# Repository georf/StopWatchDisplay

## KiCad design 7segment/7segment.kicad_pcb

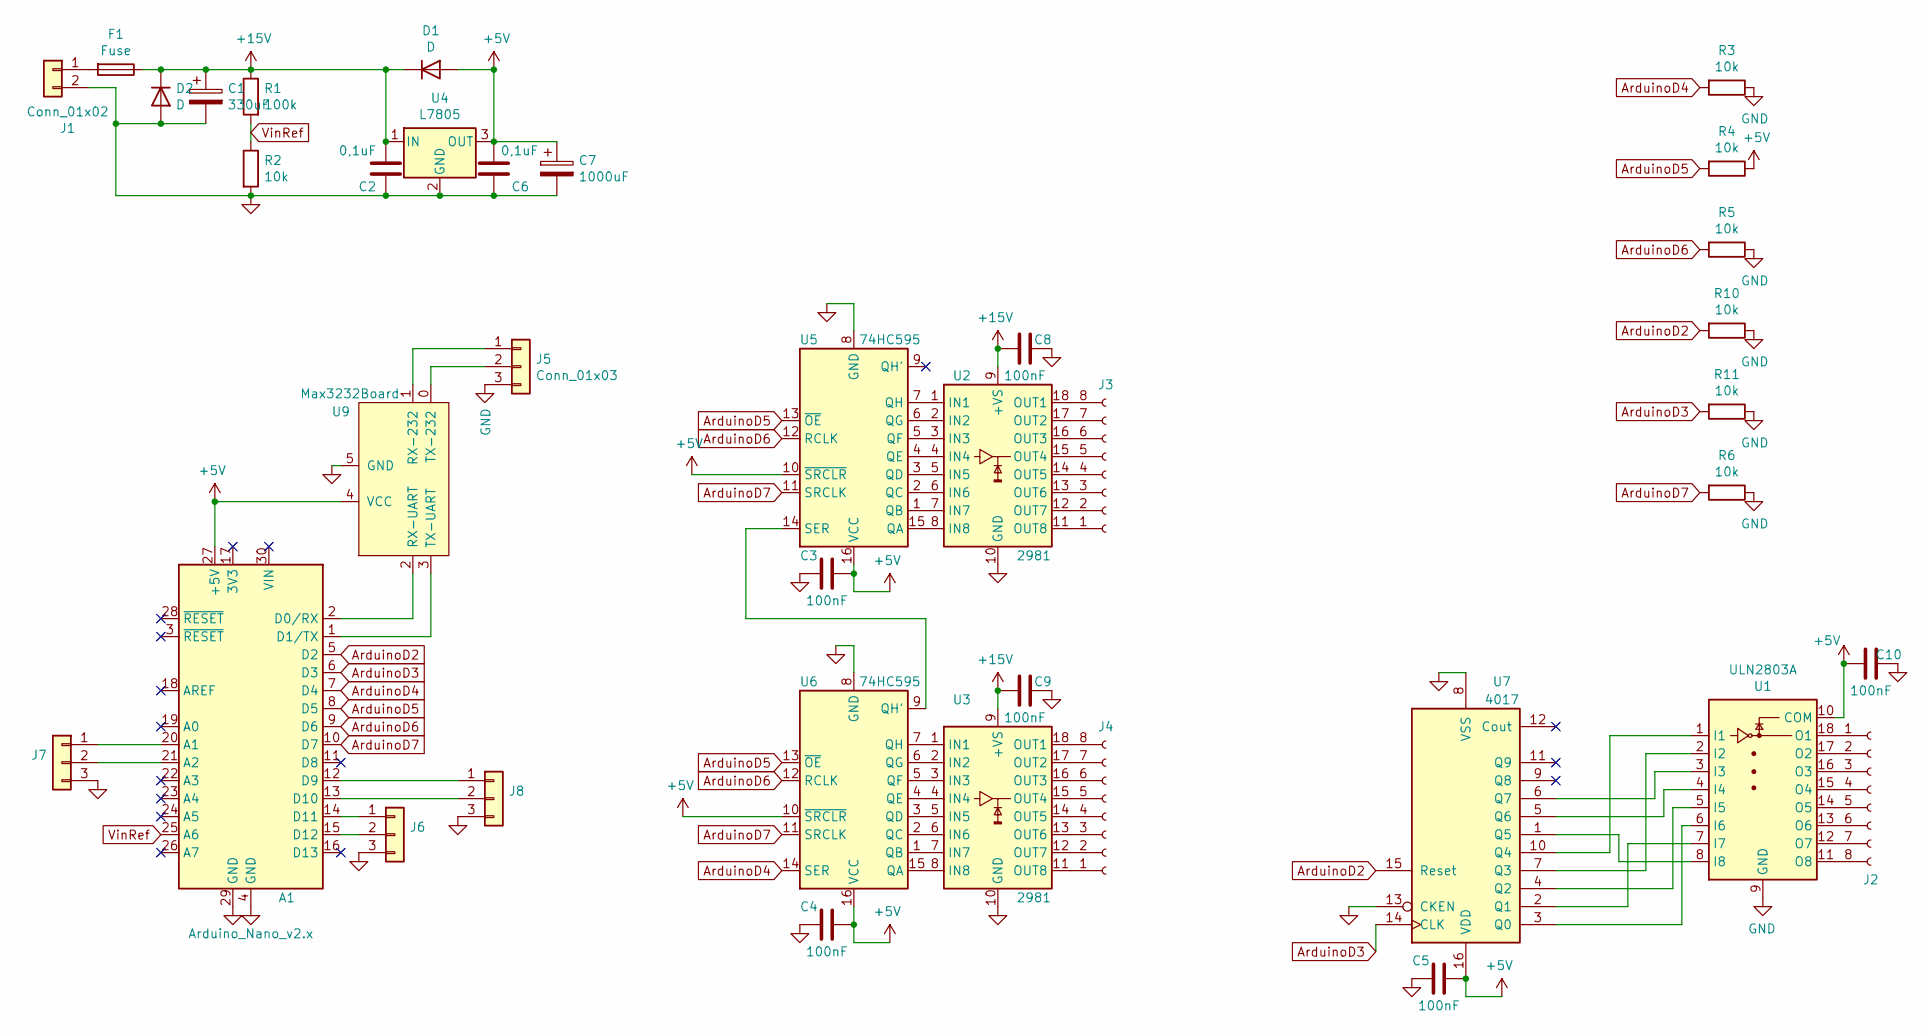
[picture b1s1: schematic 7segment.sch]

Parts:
A1: Arduino_Nano_v2.x; Arduino_Nano
C1: 330uF; CP_Radial_D10.0mm_P5.00mm
C2, C6: 0,1uF; C_Disc_D3.4mm_W2.1mm_P2.50mm
C3, C4, C5, C8, C9, C10: 100nF; C_Disc_D5.0mm_W2.5mm_P2.50mm
C7: 1000uF; CP_Radial_D10.0mm_P5.00mm
D1: D; D_A-405_P10.16mm_Horizontal
D2: D; D_A-405_P7.62mm_Horizontal
F1: Fuse
J1: Conn_01x02; Connector 2xPin
J2, J3, J4: Conn_Segments; PinSocket_1x08_P2.54mm_Vertical
J5, J6, J7, J8: Conn_01x03; Connector 3xPin
R1: 100k; Resistor, L6mm,4holes
R2, R4, R6, R11: 10k; Resistor, L6mm,5holes
R3, R10: 10k; Resistor, L6mm,4holes
R5: 10k; Resistor, L6mm,6holes
U1: ULN2803A; DIP-18_W7.62mm_LongPads
U2, U3: 2981; DIP-18_W7.62mm_LongPads
U4: L7805; TO255P1040X460X1968-3
U5, U6: 74HC595; DIP-16_W7.62mm_LongPads
U7: 4017; DIP-16_W7.62mm_LongPads
U9: Max3232Board; MAX232

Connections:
+5V: A1.27 (+5V), C3.2, C4.2, C5.2, C6.2, C7.1, C10.1, D1.2 (A), R4.1, U1.10 (COM), U4.3 (OUT), U5.10 (~SRCLR), U5.16 (VCC), U6.10 (~SRCLR), U6.16 (VCC), U7.16 (VDD), U9.4 (VCC)
+15V: C1.1, C2.2, C8.1, C9.1, D1.1 (K), D2.1 (K), F1.1, R1.1, U2.9 (+VS), U3.9 (+VS), U4.1 (IN)
ArduinoD2: A1.5 (D2), R10.2, U7.15 (Reset)
ArduinoD3: A1.6 (D3), R11.2, U7.14 (CLK)
ArduinoD4: A1.7 (D4), R3.2, U6.14 (SER)
ArduinoD5: A1.8 (D5), R4.2, U5.13 (~OE), U6.13 (~OE)
ArduinoD6: A1.9 (D6), R5.2, U5.12 (RCLK), U6.12 (RCLK)
ArduinoD7: A1.10 (D7), R6.2, U5.11 (SRCLK), U6.11 (SRCLK)
GND: A1.4 (GND), A1.29 (GND), C1.2, C2.1, C3.1, C4.1, C5.1, C6.1, C7.2, C8.2, C9.2, C10.2, D2.2 (A), J1.2, J5.3, J6.3, J7.3, J8.3, R2.2, R3.1, R5.1, R6.1, R10.1, R11.1, U1.9 (GND), U2.10 (GND), U3.10 (GND), U4.2 (GND), U5.8 (GND), U6.8 (GND), U7.8 (VSS), U7.13 (CKEN), U9.5 (GND)
unnamed: A1.1 (D1/TX), U9.3 (TX-UART)
unnamed: A1.2 (D0/RX), U9.2 (RX-UART)
unnamed: A1.12 (D9), J8.1
unnamed: A1.13 (D10), J8.2
unnamed: A1.14 (D11), J6.1
unnamed: A1.15 (D12), J6.2
unnamed: A1.20 (A1), J7.1
unnamed: A1.21 (A2), J7.2
unnamed: F1.2, J1.1
unnamed: J2.1, U1.18 (O1)
unnamed: J2.2, U1.17 (O2)
unnamed: J2.3, U1.16 (O3)
unnamed: J2.4, U1.15 (O4)
unnamed: J2.5, U1.14 (O5)
unnamed: J2.6, U1.13 (O6)
unnamed: J2.7, U1.12 (O7)
unnamed: J2.8, U1.11 (O8)
unnamed: J3.1, U2.11 (NC)
unnamed: J3.2, U2.12 (OUT7)
unnamed: J3.3, U2.13 (OUT6)
unnamed: J3.4, U2.14 (OUT5)
unnamed: J3.5, U2.15 (OUT4)
unnamed: J3.6, U2.16 (OUT3)
unnamed: J3.7, U2.17 (OUT2)
unnamed: J3.8, U2.18 (OUT1)
unnamed: J4.1, U3.11 (NC)
unnamed: J4.2, U3.12 (OUT7)
unnamed: J4.3, U3.13 (OUT6)
unnamed: J4.4, U3.14 (OUT5)
unnamed: J4.5, U3.15 (OUT4)
unnamed: J4.6, U3.16 (OUT3)
unnamed: J4.7, U3.17 (OUT2)
unnamed: J4.8, U3.18 (OUT1)
unnamed: J5.1, U9.1 (RX-232)
unnamed: J5.2, U9.0 (TX-232)
unnamed: U1.1 (I1), U7.10 (Q4)
unnamed: U1.2 (I2), U7.7 (Q3)
unnamed: U1.3 (I3), U7.6 (Q7)
unnamed: U1.4 (I4), U7.5 (Q6)
unnamed: U1.5 (I5), U7.4 (Q2)
unnamed: U1.6 (I6), U7.3 (Q0)
unnamed: U1.7 (I7), U7.2 (Q1)
unnamed: U1.8 (I8), U7.1 (Q5)
unnamed: U2.1 (IN1), U5.7 (QH)
unnamed: U2.2 (IN2), U5.6 (QG)
unnamed: U2.3 (IN3), U5.5 (QF)
unnamed: U2.4 (IN4), U5.4 (QE)
unnamed: U2.5 (IN5), U5.3 (QD)
unnamed: U2.6 (IN6), U5.2 (QC)
unnamed: U2.7 (IN7), U5.1 (QB)
unnamed: U2.8 (IN8), U5.15 (QA)
unnamed: U3.1 (IN1), U6.7 (QH)
unnamed: U3.2 (IN2), U6.6 (QG)
unnamed: U3.3 (IN3), U6.5 (QF)
unnamed: U3.4 (IN4), U6.4 (QE)
unnamed: U3.5 (IN5), U6.3 (QD)
unnamed: U3.6 (IN6), U6.2 (QC)
unnamed: U3.7 (IN7), U6.1 (QB)
unnamed: U3.8 (IN8), U6.15 (QA)
unnamed: U5.14 (SER), U6.9 (QH')
VinRef: A1.25 (A6), R1.2, R2.1

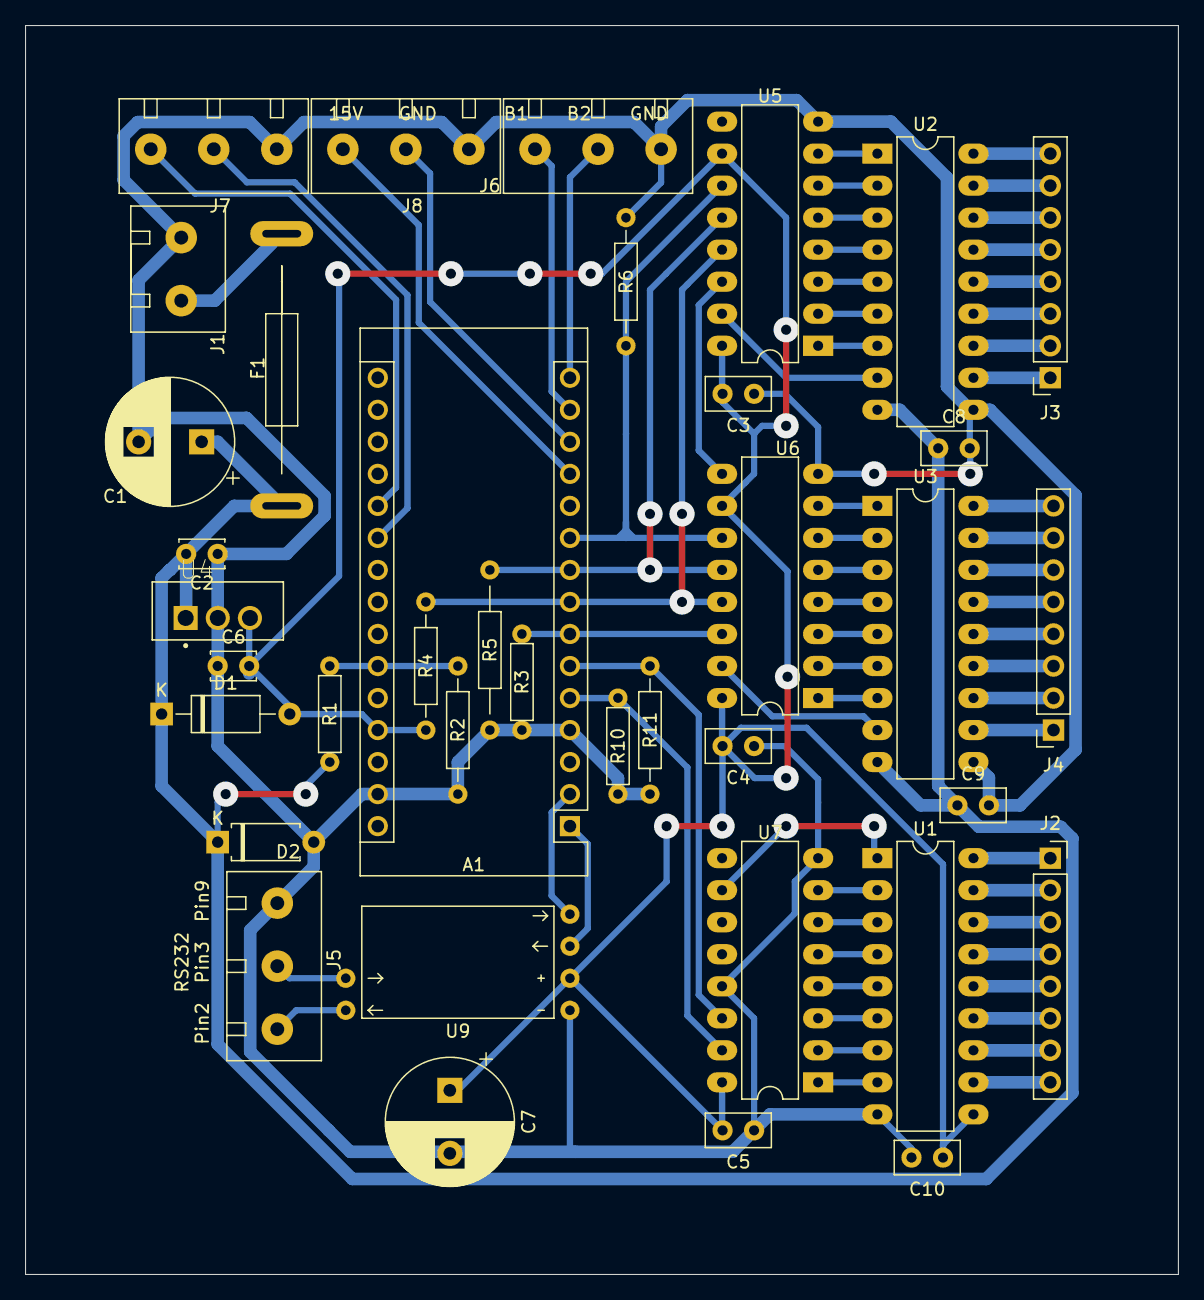
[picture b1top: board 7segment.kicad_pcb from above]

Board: 2 copper layers, 91.4 x 99.1 mm, 38 parts (0 on the bottom side), 70 nets.

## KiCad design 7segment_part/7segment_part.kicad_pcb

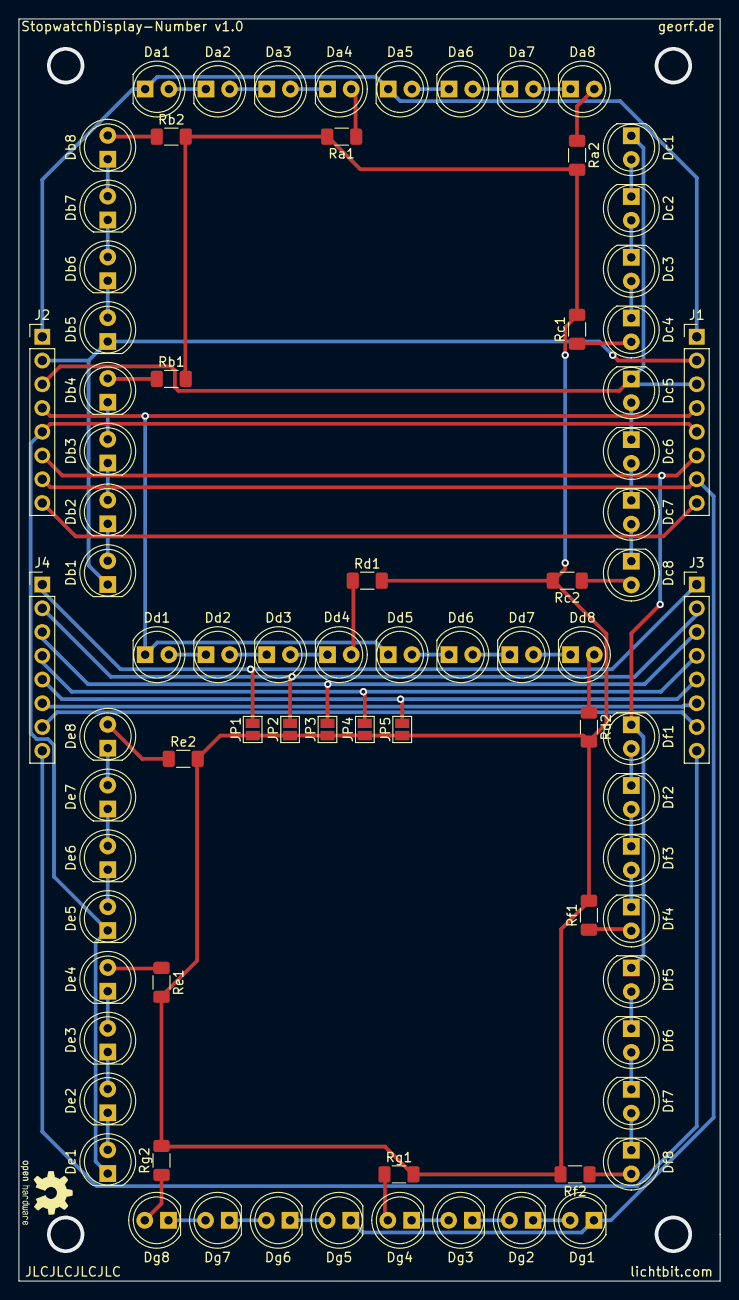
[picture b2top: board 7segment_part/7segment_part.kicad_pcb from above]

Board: 2 copper layers, 75.0 x 135.0 mm, 79 parts (0 on the bottom side), 73 nets.

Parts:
Da1, Da2, Da3, Da4, Da5, Da6, Da7, Da8: LED; LED_D5.0mm_Clear
Db1, Db2, Db3, Db4, Db5, Db6, Db7, Db8: LED; LED_D5.0mm_Clear
Dc1, Dc2, Dc3, Dc4, Dc5, Dc6, Dc7, Dc8: LED; LED_D5.0mm_Clear
Dd1, Dd2, Dd3, Dd4, Dd5, Dd6, Dd7, Dd8: LED; LED_D5.0mm_Clear
De1, De2, De3, De4, De5, De6, De7, De8: LED; LED_D5.0mm_Clear
Df1, Df2, Df3, Df4, Df5, Df6, Df7, Df8: LED; LED_D5.0mm_Clear
Dg1, Dg2, Dg3, Dg4, Dg5, Dg6, Dg7, Dg8: LED; LED_D5.0mm_Clear
J1, J2: Segments; PinHeader_1x08_P2.54mm_Vertical
J3, J4: Numbers; PinHeader_1x08_P2.54mm_Vertical
JP1, JP2, JP3, JP4, JP5: SolderJumper_2_Open; SolderJumper-2_P1.3mm_Open_Pad1.0x1.5mm
Ra1, Ra2: R; R_1206_3216Metric_Pad1.30x1.75mm_HandSolder
Rb1, Rb2: R; R_1206_3216Metric_Pad1.30x1.75mm_HandSolder
Rc1, Rc2: R; R_1206_3216Metric_Pad1.30x1.75mm_HandSolder
Rd1, Rd2: R; R_1206_3216Metric_Pad1.30x1.75mm_HandSolder
Re1, Re2: R; R_1206_3216Metric_Pad1.30x1.75mm_HandSolder
Rf1, Rf2: R; R_1206_3216Metric_Pad1.30x1.75mm_HandSolder
Rg1, Rg2: R; R_1206_3216Metric_Pad1.30x1.75mm_HandSolder

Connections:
unnamed: Da1.1, Da5.1, J1.1, J2.1
unnamed: Da1.2, Da2.1
unnamed: Da2.2, Da3.1
unnamed: Da3.2, Da4.1
unnamed: Da4.2, Ra1.1
unnamed: Da5.2, Da6.1
unnamed: Da6.2, Da7.1
unnamed: Da7.2, Da8.1
unnamed: Da8.2, Ra2.1
unnamed: Db1.1, Db5.1, J1.2, J2.2
unnamed: Db1.2, Db2.1
unnamed: Db2.2, Db3.1
unnamed: Db3.2, Db4.1
unnamed: Db4.2, Rb1.1
unnamed: Db5.2, Db6.1
unnamed: Db6.2, Db7.1
unnamed: Db7.2, Db8.1
unnamed: Db8.2, Rb2.1
unnamed: Dc1.1, Dc5.1, J1.3, J2.3
unnamed: Dc1.2, Dc2.1
unnamed: Dc2.2, Dc3.1
unnamed: Dc3.2, Dc4.1
unnamed: Dc4.2, Rc1.1
unnamed: Dc5.2, Dc6.1
unnamed: Dc6.2, Dc7.1
unnamed: Dc7.2, Dc8.1
unnamed: Dc8.2, Rc2.1
unnamed: Dd1.1, Dd5.1, J1.4, J2.4
unnamed: Dd1.2, Dd2.1
unnamed: Dd2.2, Dd3.1
unnamed: Dd3.2, Dd4.1
unnamed: Dd4.2, Rd1.1
unnamed: Dd5.2, Dd6.1
unnamed: Dd6.2, Dd7.1
unnamed: Dd7.2, Dd8.1
unnamed: Dd8.2, Rd2.1
unnamed: De1.1, De5.1, J1.5, J2.5
unnamed: De1.2, De2.1
unnamed: De2.2, De3.1
unnamed: De3.2, De4.1
unnamed: De4.2, Re1.1
unnamed: De5.2, De6.1
unnamed: De6.2, De7.1
unnamed: De7.2, De8.1
unnamed: De8.2, Re2.1
unnamed: Df1.1, Df5.1, J1.6, J2.6
unnamed: Df1.2, Df2.1
unnamed: Df2.2, Df3.1
unnamed: Df3.2, Df4.1
unnamed: Df4.2, Rf1.1
unnamed: Df5.2, Df6.1
unnamed: Df6.2, Df7.1
unnamed: Df7.2, Df8.1
unnamed: Df8.2, Rf2.1
unnamed: Dg1.1, Dg5.1, J1.7, J2.7
unnamed: Dg1.2, Dg2.1
unnamed: Dg2.2, Dg3.1
unnamed: Dg3.2, Dg4.1
unnamed: Dg4.2, Rg1.1
unnamed: Dg5.2, Dg6.1
unnamed: Dg6.2, Dg7.1
unnamed: Dg7.2, Dg8.1
unnamed: Dg8.2, Rg2.1
unnamed: J1.8, J2.8
unnamed: J3.1, J4.1, JP1.2
unnamed: J3.2, J4.2, JP2.2
unnamed: J3.3, J4.3, JP3.2
unnamed: J3.4, J4.4, JP4.2
unnamed: J3.5, J4.5, JP5.2
unnamed: J3.6, J4.6
unnamed: J3.7, J4.7
unnamed: J3.8, J4.8
unnamed: JP1.1, JP2.1, JP3.1, JP4.1, JP5.1, Ra1.2, Ra2.2, Rb1.2, Rb2.2, Rc1.2, Rc2.2, Rd1.2, Rd2.2, Re1.2, Re2.2, Rf1.2, Rf2.2, Rg1.2, Rg2.2

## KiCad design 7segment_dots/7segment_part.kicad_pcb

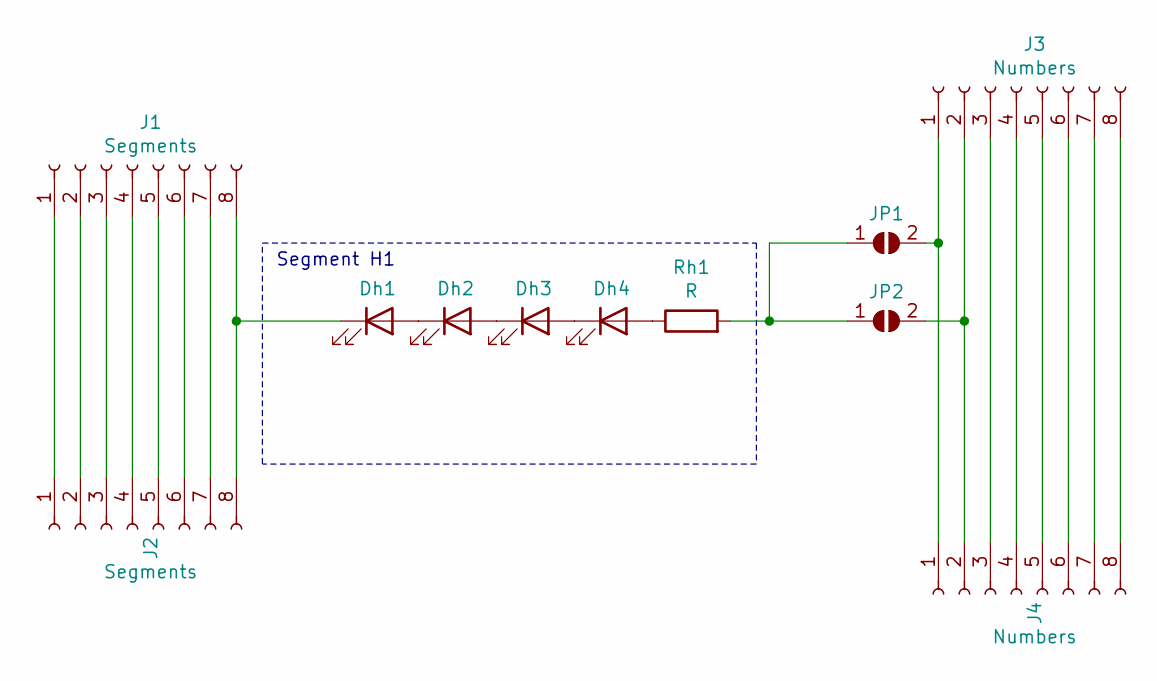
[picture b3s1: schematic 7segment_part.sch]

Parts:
Dh1, Dh2, Dh3, Dh4: LED; LED_D5.0mm_Clear
J1, J2: Segments; PinHeader_1x08_P2.54mm_Vertical
J3, J4: Numbers; PinHeader_1x08_P2.54mm_Vertical
JP1, JP2: SolderJumper_2_Open; SolderJumper-2_P1.3mm_Open_Pad1.0x1.5mm
Rh1: R; R_1206_3216Metric_Pad1.30x1.75mm_HandSolder

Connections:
unnamed: Dh1.1 (K), J1.8, J2.8
unnamed: Dh1.2 (A), Dh2.1 (K)
unnamed: Dh2.2 (A), Dh3.1 (K)
unnamed: Dh3.2 (A), Dh4.1 (K)
unnamed: Dh4.2 (A), Rh1.1
unnamed: J1.1, J2.1
unnamed: J1.2, J2.2
unnamed: J1.3, J2.3
unnamed: J1.4, J2.4
unnamed: J1.5, J2.5
unnamed: J1.6, J2.6
unnamed: J1.7, J2.7
unnamed: J3.1, J4.1, JP1.2 (B)
unnamed: J3.2, J4.2, JP2.2 (B)
unnamed: J3.3, J4.3
unnamed: J3.4, J4.4
unnamed: J3.5, J4.5
unnamed: J3.6, J4.6
unnamed: J3.7, J4.7
unnamed: J3.8, J4.8
unnamed: JP1.1 (A), JP2.1 (A), Rh1.2

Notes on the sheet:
Segment H1

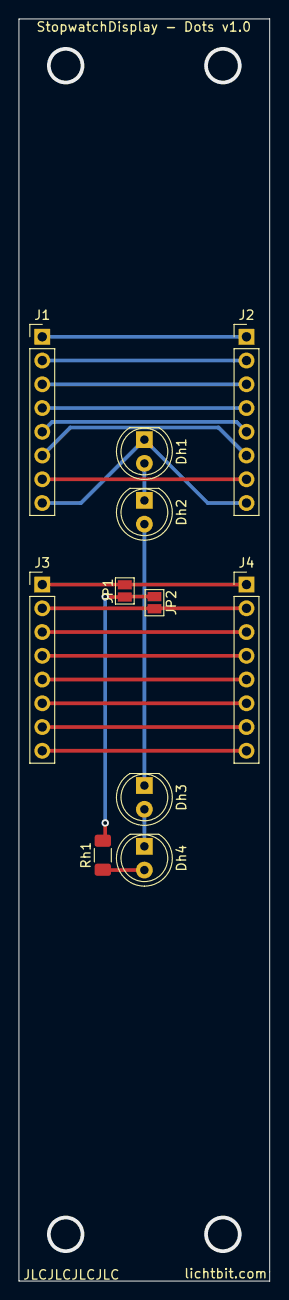
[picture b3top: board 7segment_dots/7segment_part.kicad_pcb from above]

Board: 2 copper layers, 26.8 x 135.0 mm, 11 parts (0 on the bottom side), 21 nets.

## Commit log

2020-10-23 KiCad-Projekt: Teilanzeige Punkte
2020-10-23 KiCad-Projekt: Teilanzeige Nummer
2020-10-23 KiCad-Projekt: Hauptplatine
2020-10-23 C-Projekt für Arduino
2020-10-23 Cache ignorieren
2021-03-15 C-Projekt: Version 1
2021-03-15 Fotos ignorieren
2021-03-15 KiCad: Platinen Version 1
2021-03-15 Stoppuhr-Computer mit Arduino simulieren
2021-03-15 Datasheets ignorieren
2021-08-31 Anlage von Platz-Gamstädt über Serielle Schnittstelle ermöglichen
2021-08-31 Anzeige verbessern
2021-10-09 Konvertierung der Zeiten korrigieren
